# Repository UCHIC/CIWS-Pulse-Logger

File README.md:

# CIWS-Pulse-Datalogger

This repository contains hardware and software designs for the Pulse-Datalogger, a device that can be used to collect high resolution water use data on magnetically-driven residential water meters. The datalogger is designed to read magnetic field information from a magnetometer sensor attached to a magnetically-driven, positive-displacement water meter. 

Firmware: The Firmware folder contains code written for the datalogger.

Hardware: The Hardware folder contains hardware design information for off-the-shelf components as well as a 
manufacturable PCB.

## Operation
The device is made up of an ATMEGA328P microcontroller chip and three peripherial systems. These are an RTC(Real Time Clock), Magnetometer, and SD Card. The magnetometer reads magnetic data from the water meter and inturrupts the microcontroller when a threshold is passed. The RTC minimizes time drift by inturrupting the micronctoller at the start of every day. On this inturrupt it resets its time-keeping values to sync it with the RTC time. The SD Card stores water pulse data.

## Setup
Strap the device to the meter and connect the device to a computer via USB-Serial connector. Send a character to start communication. Answer the questions asked by the device with a `y` or `n` and fill in any requested information. Immediatly after answering those two questions the device will start to measure magnetic data to set the threshold for the magnetometer. Water must be turned on in the house to properly configure the thresholds. If you miss the calibration time restart the device and try again. After calibration the device automatically begins recording water data to the SD Card. To collect water data hit the restatrt button on the device and collect the SD Card. Water data is organised into different files for each day of data recorded. Each file contains a file header with the site ID, device ID, and date and time of data collection started. After the header each pulse is stored on a new line and is represented as an integer value. The interger value represents the milliseconds since the last pulse. 

## Cyberinfrastructure for Intelligent Water Supply (CIWS) 

CIWS is a project funded by the U.S. National Science Foundation to develop cyberinfrastructure for smart water metering and high resolution water-use data collection. We are developing systems for high resolution residential water consumption data collection, processing and analysis.

## Sponsors and Credits

This work was supported by National Science Foundation Grant [CBET 1552444](https://www.nsf.gov/awardsearch/showAward?AWD_ID=1552444). Any opinions, findings, and conclusions or recommendations expressed in this material are those of the author(s) and do not necessarily reflect the views of the National Science Foundation.

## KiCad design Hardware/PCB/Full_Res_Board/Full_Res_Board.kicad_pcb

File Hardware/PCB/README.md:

# Full Resolution PCB Board
Instructions, fabrication files, and parts list for manufacturing a full resolution pcb board.

## Parts List
CSV of components available in [Hardware/PCB/KiCad/parts_list.csv](https://github.com/UCHIC/CIWS-Pulse-Logger/blob/main/Hardware/PCB/KiCad/parts_list.csv).

## Instructions
For convenience several common fabrication files have been generated and can be found in [Hardware/PCB/KiCad/FabFiles](https://github.com/UCHIC/CIWS-Pulse-Logger/tree/main/Hardware/PCB/KiCad/FabFiles).
If all the files required by your manufacturer are there, download the `.zip` file in that directory and submit it.

If your manufacturer has questions about parts direct them to the [parts csv](https://github.com/UCHIC/CIWS-Pulse-Logger/blob/main/Hardware/PCB/KiCad/parts_list.csv).

If additional fabrication files are needed download the files in [Hardware/PCB/KiCad/ProjectFiles](https://github.com/UCHIC/CIWS-Pulse-Logger/tree/main/Hardware/PCB/KiCad/ProjectFiles). In KiCad open the `.pro` file and follow your manufatures instructions for generating fabrication files.

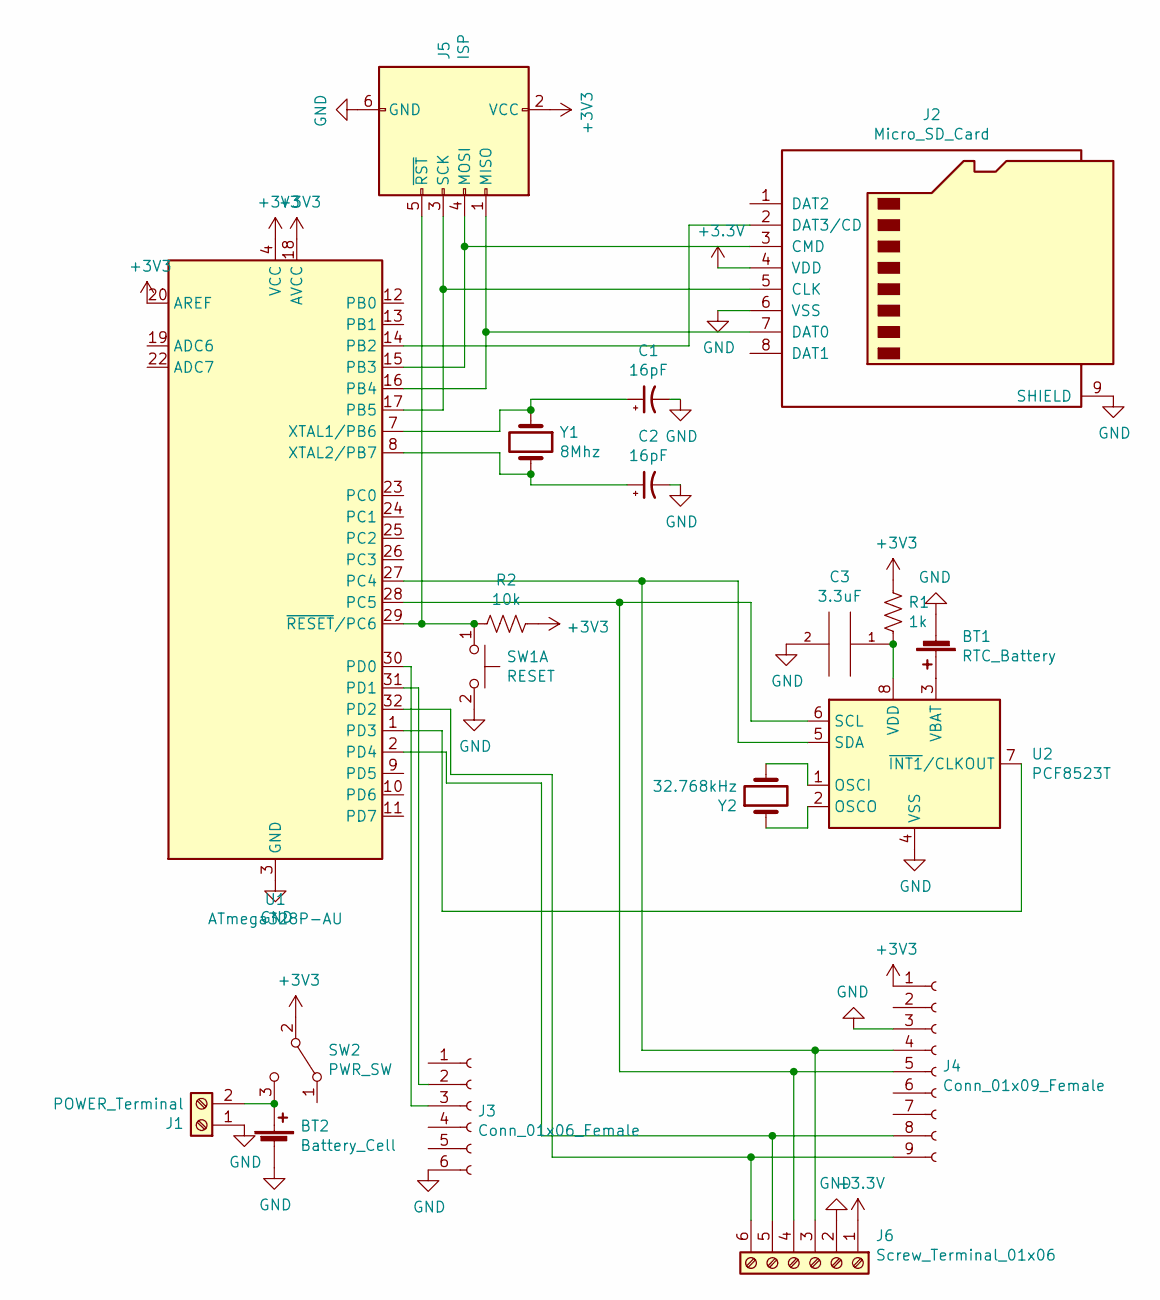
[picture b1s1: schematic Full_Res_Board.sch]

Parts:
BT1: RTC_Battery; BatteryHolder_Keystone_3000_1x12mm
BT2: Battery_Cell; BatteryHolder_MPD_BH-18650-PC2
C1, C2: 16pF; C_0805_2012Metric
C3: 3.3uF; C_0805_2012Metric
J1: POWER_Terminal; TerminalBlock_Phoenix_MPT-0,5-2-2.54_1x02_P2.54mm_Horizontal
J2: Micro_SD_Card; microSD_HC_Wuerth_693072010801
J3: Conn_01x06_Female; PinHeader_1x06_P2.54mm_Vertical
J4: Conn_01x09_Female; PinHeader_1x09_P2.54mm_Vertical
J5: ISP; PinHeader_2x03_P2.54mm_Vertical
J6: Screw_Terminal_01x06; TerminalBlock_Phoenix_MPT-0,5-6-2.54_1x06_P2.54mm_Horizontal
R1: 1k; R_0805_2012Metric
R2: 10k; LED_0805_2012Metric_Castellated
SW1: RESET; SW_TH_Tactile_Omron_B3F-10xx
SW2: PWR_SW; SW_Slide_1P2T_CK_OS102011MS2Q
U1: ATmega328P-AU; TQFP-32_7x7mm_P0.8mm
U2: PCF8523T; SOIC-8_3.9x4.9mm_P1.27mm
Y1: 8Mhz; Crystal_SMD_TXC_AX_8045-2Pin_8.0x4.5mm
Y2: 32.768kHz; Crystal_SMD_EuroQuartz_EQ161-2Pin_3.2x1.5mm_HandSoldering

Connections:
GND: BT1.2 (-), BT2.2 (-), C1.2, C2.2, C3.2, J1.1, J2.6 (VSS), J2.9 (SHIELD), J3.6, J4.3, J5.6 (GND), J6.2, SW1.2 (D), U1.3 (GND), U1.5 (GND), U1.21 (GND), U2.4 (VSS)
unnamed: BT1.1 (+), U2.3 (VBAT)
unnamed: BT2.1 (+), J1.2, SW2.3 (C)
unnamed: C1.1, U1.7 (XTAL1/PB6), Y1.1
unnamed: C2.1, U1.8 (XTAL2/PB7), Y1.2
unnamed: C3.1, R1.2, U2.8 (VDD)
unnamed: J2.2 (DAT3/CD), U1.14 (PB2)
unnamed: J2.3 (CMD), J5.4 (MOSI), U1.15 (PB3)
unnamed: J2.5 (CLK), J5.3 (SCK), U1.17 (PB5)
unnamed: J2.7 (DAT0), J5.1 (MISO), U1.16 (PB4)
unnamed: J3.2, U1.31 (PD1)
unnamed: J3.3, U1.30 (PD0)
unnamed: J4.4, J6.3, U1.27 (PC4), U2.5 (SDA)
unnamed: J4.5, J6.4, U1.28 (PC5), U2.6 (SCL)
unnamed: J4.8, J6.5, U1.2 (PD4)
unnamed: J4.9, J6.6, U1.32 (PD2)
unnamed: J5.5 (~RST), R2.2, SW1.1 (C), U1.29 (~RESET~/PC6)
unnamed: U1.1 (PD3), U2.7 (~INT1~/CLKOUT)
unnamed: U2.1 (OSCI), Y2.2
unnamed: U2.2 (OSCO), Y2.1

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
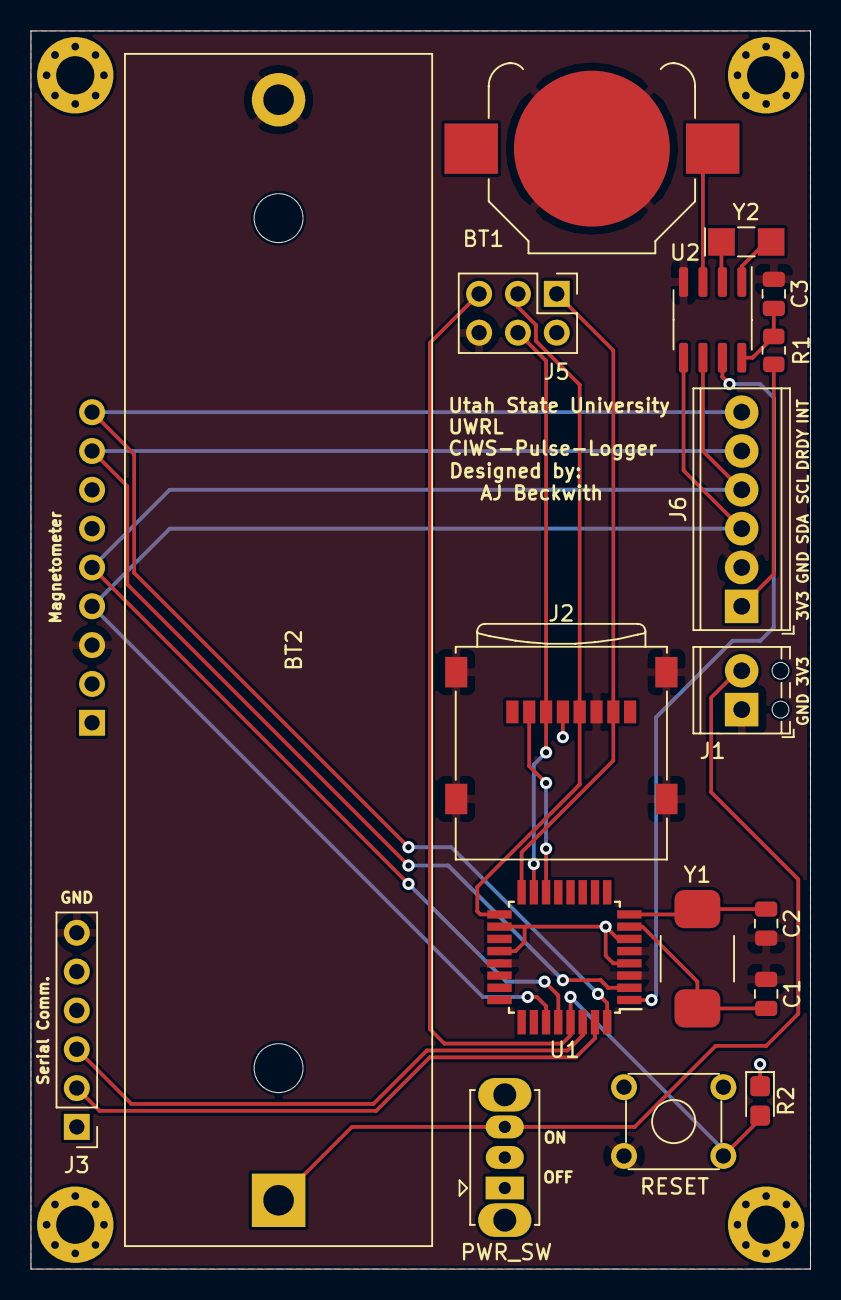
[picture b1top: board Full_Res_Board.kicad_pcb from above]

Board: 2 copper layers, 51.0 x 81.0 mm, 19 parts (1 on the bottom side), 21 nets.

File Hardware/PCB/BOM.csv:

"Id";"Designator";"Package";"Quantity";"Designation";"Supplier and ref";
1;"J6";"TerminalBlock_Phoenix_MPT-0,5-6-2.54_1x06_P2.54mm_Horizontal";1;"Screw_Terminal_01x06";;;
2;"REF**,REF**,REF**,REF**";"MountingHole_2.5mm_Pad_Via";4;"MountingHole_2.5mm_Pad_Via";;;
3;"BT2";"BatteryHolder_MPD_BH-18650-PC2";1;"Battery_Cell";;;
4;"J4";"PinHeader_1x09_P2.54mm_Vertical";1;"Conn_01x09_Female";;;
5;"J3";"PinHeader_1x06_P2.54mm_Vertical";1;"Conn_01x06_Female";;;
6;"Y2";"Crystal_SMD_EuroQuartz_EQ161-2Pin_3.2x1.5mm_HandSoldering";1;"32.768kHz";;;
7;"Y1";"Crystal_SMD_TXC_AX_8045-2Pin_8.0x4.5mm";1;"8Mhz";;;
8;"U2";"SOIC-8_3.9x4.9mm_P1.27mm";1;"PCF8523T";;;
9;"U1";"TQFP-32_7x7mm_P0.8mm";1;"ATmega328P-AU";;;
10;"SW2";"SW_Slide_1P2T_CK_OS102011MS2Q";1;"PWR_SW";;;
11;"SW1";"SW_TH_Tactile_Omron_B3F-10xx";1;"RESET";;;
12;"R2";"LED_0805_2012Metric_Castellated";1;"10k";;;
13;"R1";"R_0805_2012Metric";1;"1k";;;
14;"J5";"PinHeader_2x03_P2.54mm_Vertical";1;"ISP";;;
15;"J2";"microSD_HC_Wuerth_693072010801";1;"Micro_SD_Card";;;
16;"J1";"TerminalBlock_Phoenix_MPT-0,5-2-2.54_1x02_P2.54mm_Horizontal";1;"POWER_Terminal";;;
17;"C3";"C_0805_2012Metric";1;"3.3uF";;;
18;"C2,C1";"C_0805_2012Metric";2;"16pF";;;
19;"BT1";"BatteryHolder_Keystone_3000_1x12mm";1;"RTC_Battery";;;

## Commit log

2022-02-21 Rename Full_Resolution_Device_Develop.ino to Full_Resolution_Device.ino
2022-02-21 update file name
2022-03-01 remove testing code
2022-03-14 board
2022-03-15 hardware
2022-03-22 update hardware
2022-03-22 rename
2022-03-22 Rename Full_Res_Board.csv to parts_list.csv
2022-03-22 restructure
2022-06-29 Create fp-info-cache
2022-06-29 Update off the shelf
